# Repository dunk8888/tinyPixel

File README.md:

# tinyPixel

tinyPixel is a compact, open-source, I2C-ready, BlinkM-compatible high-power RGB LED driver that can be individually pre-programmed or daisy-chainned and controlled by an Arduino or other microcontroller platform (like my Lumiboard!). tinyPixel uses the open-source cyz_rgb firmware to emulate the behavior of BlinkM modules, so it can be used with BlinkM software.

BlinkM modules are great, but quite expensive, especially if you want to use them in an installation (as they were intended). DIY alternatives, such as the Ghetto Pixel, are great but can be a burden to assemble at scale and are limited in the types of LEDs they use. I wanted something that was cheap, small and would be easy to assemble in a hurry.

## Board features
* Standard BlinkM-style interface (4-pin 0.1" male header for +, -, c and d lines).
* On-board 2W power resistors, so that 3W and 5W RGB LEDs can be driven.
* On-board ATTiny85 with cyz_rgb preloaded.
* On-board ULN2003 Darlington transistor array to sink large amounts of current for the RGB LED.
* 4-pin 0.1" male header to decouple RGB LED from main board (R,G, B and + lines).
* On-board 10uF capacitor to smooth the power out on each board.
* 4-pin Molex / ATX power connector to supply power.

## More information
Author's website: http://jason-webb.info
Project wiki: http://jason-webb.info/wiki/index.php?title=TinyPixel

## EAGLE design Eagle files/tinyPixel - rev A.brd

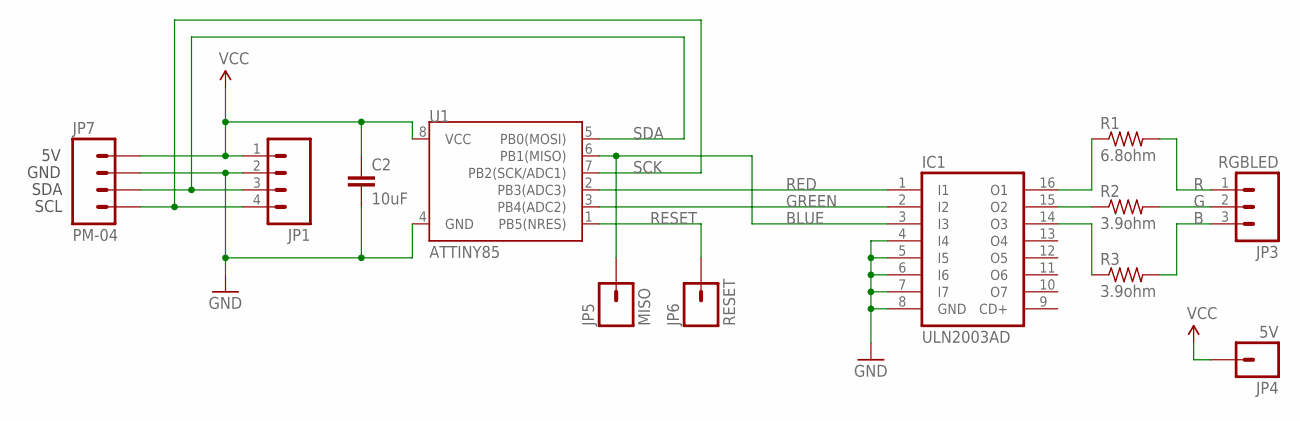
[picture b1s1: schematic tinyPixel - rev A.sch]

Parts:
C2: 10uF; 0805
IC1: ULN2003AD; SO16
JP1: M04PTH; 1X04
JP3: RGBLED; 1X03
JP4: 5V; 1X01
JP5: MISO; M01-SMD
JP6: RESET; M01-SMD
JP7: PM-04
R1: 6.8ohm; 0411/12
R2, R3: 3.9ohm; 0411/12
U1: ATTINY85; SO08-EIAJ

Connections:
B: JP3.3, R3.2
BLUE: IC1.3 (I3), JP5.P$2, U1.6 (PB1(MISO))
G: JP3.2, R2.2
GND: C2.2, IC1.4 (I4), IC1.5 (I5), IC1.6 (I6), IC1.7 (I7), IC1.8 (GND), JP1.2, JP7.P$3 (3), U1.4 (GND)
GREEN: IC1.2 (I2), U1.3 (PB4(ADC2))
unnamed: IC1.15 (O2), R2.1
unnamed: IC1.14 (O3), R3.1
unnamed: IC1.16 (O1), R1.1
R: JP3.1, R1.2
RED: IC1.1 (I1), U1.2 (PB3(ADC3))
RESET: JP6.P$2, U1.1 (PB5(NRES))
SCK: JP1.4, JP7.P$1 (1), U1.7 (PB2(SCK/ADC1))
SDA: JP1.3, JP7.P$2 (2), U1.5 (PB0(MOSI))
VCC: C2.1, JP1.1, JP4.1, JP7.P$4 (4), U1.8 (VCC)

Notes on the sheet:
GND
SDA
SCL

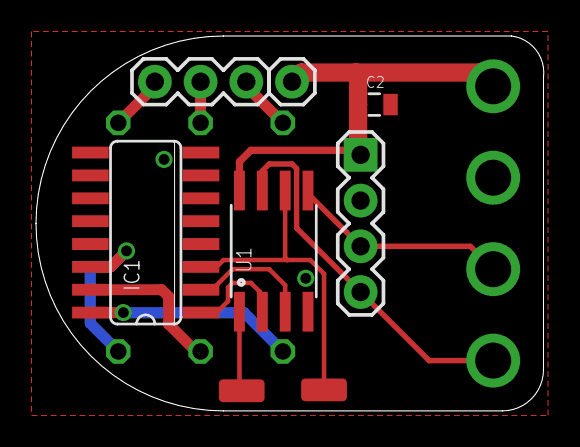
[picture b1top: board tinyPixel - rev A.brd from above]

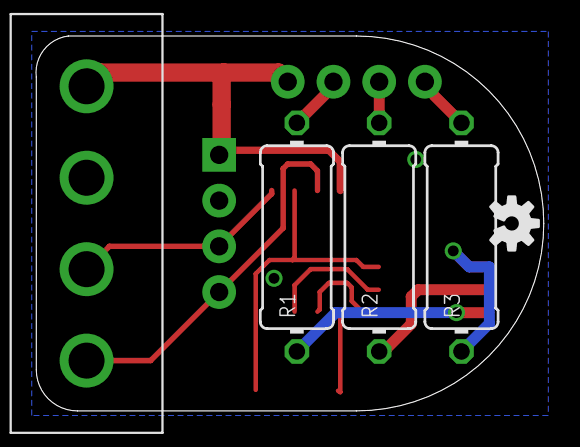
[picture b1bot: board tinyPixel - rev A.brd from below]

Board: 2 copper layers, 28.2 x 20.8 mm, 13 parts (5 on the bottom side), 14 nets.

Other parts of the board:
U$1: OSHW-LOGO-S

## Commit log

2013-01-04 Rev A board files, BOM, README updates
2013-01-04 README update
2013-01-05 Updated Eagle files, BOM and Gerbers

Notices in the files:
parts and their libraries:
SparkFun-DigitalIC: Licensing: CC v3.0 Share-Alike You are welcome to use this library for commercial purposes.
